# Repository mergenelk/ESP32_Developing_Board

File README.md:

# ESP32_Developing_Board
This project is unlicensed because it is very old.

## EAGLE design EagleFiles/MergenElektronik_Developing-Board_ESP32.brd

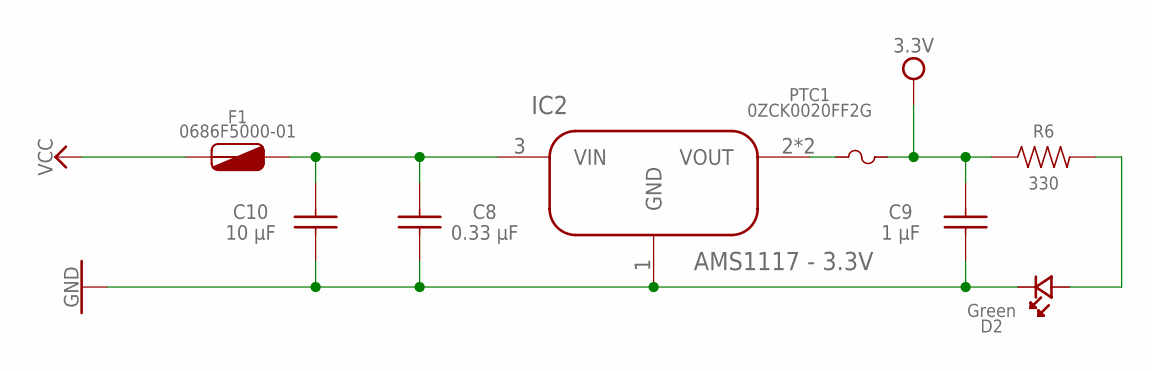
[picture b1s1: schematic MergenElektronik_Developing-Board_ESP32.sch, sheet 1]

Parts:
C8: 0.33 µF; 0603
C9: 1 µF; 0603
C10: 10 µF; 0603
D2: Green; 0603_GREEN
F1: 0686F5000-01; 0603
IC2: AMS1117 - 3.3V; SOT-223
PTC1: 0ZCK0020FF2G; 0805
R6: 330; 0603

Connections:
3V3: C9.1, PTC1.2, R6.1; also elsewhere on the board
GND: C8.2, C9.2, C10.2, D2.2 (KATOT), IC2.1 (GND); also elsewhere on the board
unnamed: D2.1 (ANOT), R6.2
unnamed: C8.1, C10.1, F1.2, IC2.3 (VIN)
unnamed: IC2.2 (VOUT), IC2.4 (VOUT), PTC1.1
VCC: F1.1; also elsewhere on the board

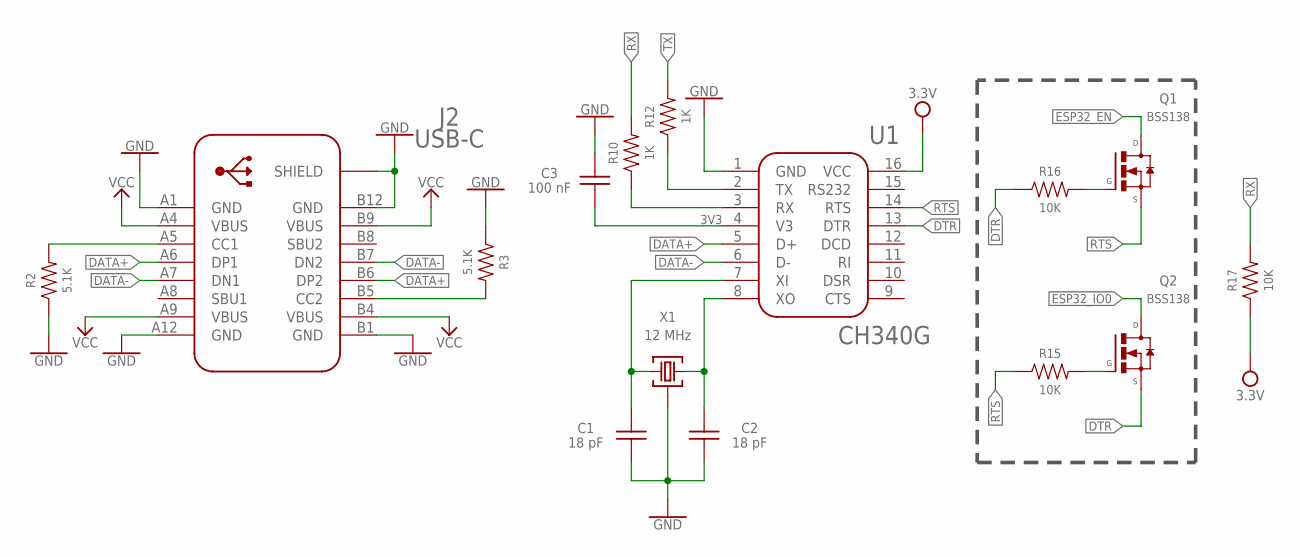
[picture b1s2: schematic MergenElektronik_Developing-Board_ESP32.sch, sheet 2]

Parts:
C1, C2: 18 pF; 0603
C3: 100 nF; 0603
J2: USB-C; USB4105
Q1, Q2: BSS138; SOT-23
R2, R3: 5.1K; 0603
R10, R12: 1K; 0603
R15, R16, R17: 10K; 0603
U1: CH340G; SOIC-16
X1: 12 MHz; 4-SMD

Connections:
3V3: C3.2, R17.1, U1.4 (V3), U1.16 (VCC); also elsewhere on the board
DATA+: J2.A6 (DP1), J2.B6 (DP2), U1.5 (D+)
DATA-: J2.A7 (DN1), J2.B7 (DN2), U1.6 (D-)
DTR: Q2.2 (S), R16.1, U1.13 (DTR)
ESP32_EN: Q1.3 (D); also elsewhere on the board
ESP32_IO0: Q2.3 (D); also elsewhere on the board
GND: C1.2, C2.2, C3.1, J2.A1 (GND), J2.A12 (GND), J2.B1 (GND), J2.B12 (GND), J2.SH1 (SHIELD), J2.SH2 (SHIELD), J2.SH3 (SHIELD), J2.SH4 (SHIELD), R2.1, R3.1, U1.1 (GND), X1.GND@1, X1.GND@2; also elsewhere on the board
unnamed: J2.A5 (CC1), R2.2
unnamed: J2.B5 (CC2), R3.2
unnamed: C1.1, U1.7 (XI), X1.3
unnamed: C2.1, U1.8 (XO), X1.1
unnamed: Q2.1 (G), R15.2
unnamed: R10.1, U1.3 (RX)
unnamed: R12.1, U1.2 (TX)
unnamed: Q1.1 (G), R16.2
RTS: Q1.2 (S), R15.1, U1.14 (RTS)
RX: R10.2, R17.2; also elsewhere on the board
TX: R12.2; also elsewhere on the board
VCC: J2.A4 (VBUS), J2.A9 (VBUS), J2.B4 (VBUS), J2.B9 (VBUS); also elsewhere on the board

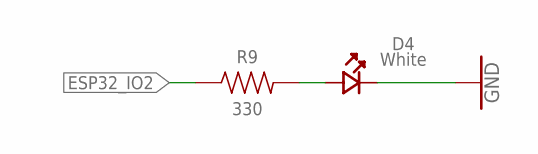
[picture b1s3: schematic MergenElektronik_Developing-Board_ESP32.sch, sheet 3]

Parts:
D4: White; 0603_WHİTE
R9: 330; 0603

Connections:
ESP32_IO2: R9.1; also elsewhere on the board
GND: D4.2 (KATOT); also elsewhere on the board
unnamed: D4.1 (ANOT), R9.2

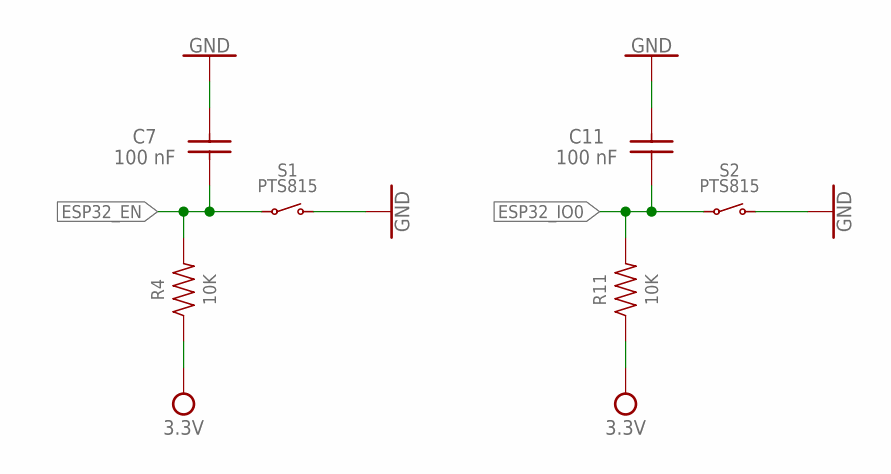
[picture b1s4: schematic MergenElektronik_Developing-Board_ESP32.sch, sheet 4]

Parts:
C7, C11: 100 nF; 0603
R4, R11: 10K; 0603
S1, S2: PTS815

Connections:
3V3: R4.1, R11.1; also elsewhere on the board
ESP32_EN: C7.2, R4.2, S1.1 (PASS1), S1.2 (PASS1); also elsewhere on the board
ESP32_IO0: C11.2, R11.2, S2.1 (PASS1), S2.2 (PASS1); also elsewhere on the board
GND: C7.1, C11.1, S1.3 (PASS2), S1.4 (PASS2), S2.3 (PASS2), S2.4 (PASS2); also elsewhere on the board

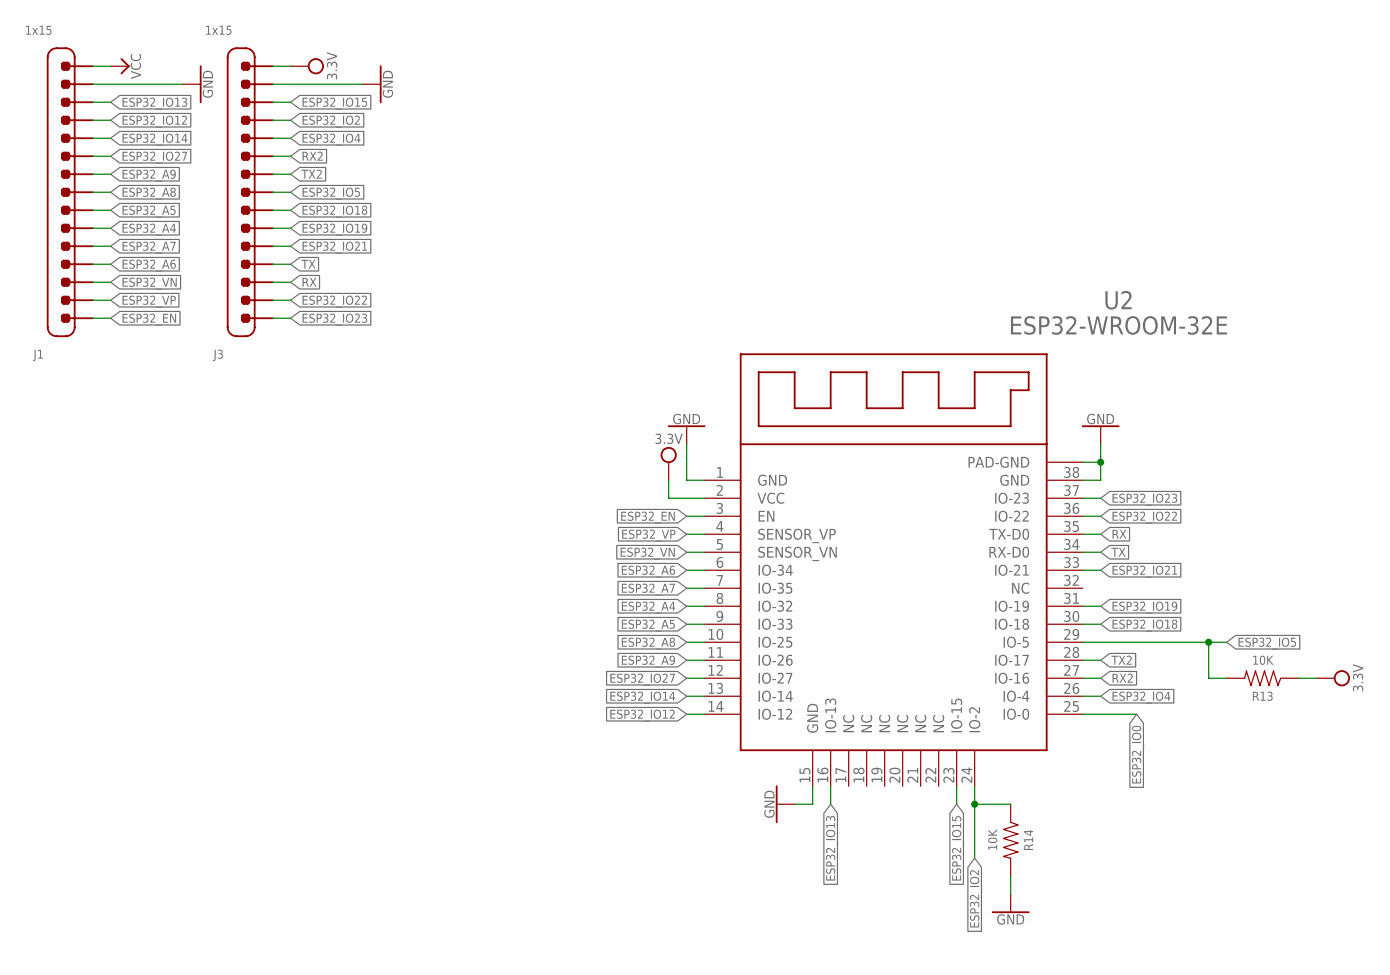
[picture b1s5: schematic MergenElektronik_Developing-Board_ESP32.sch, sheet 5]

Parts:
J1, J3: 1x15; HEADER_1X15
R13, R14: 10K; 0603
U2: ESP32-WROOM-32E; 38-SMD_MODULE

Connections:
3V3: J3.1, R13.1, U2.2 (VCC); also elsewhere on the board
ESP32_A4: J1.10, U2.8 (IO-32)
ESP32_A5: J1.9, U2.9 (IO-33)
ESP32_A6: J1.12, U2.6 (IO-34)
ESP32_A7: J1.11, U2.7 (IO-35)
ESP32_A8: J1.8, U2.10 (IO-25)
ESP32_A9: J1.7, U2.11 (IO-26)
ESP32_EN: J1.15, U2.3 (EN); also elsewhere on the board
ESP32_IO0: U2.25 (IO-0); also elsewhere on the board
ESP32_IO2: J3.4, R14.1, U2.24 (IO-2); also elsewhere on the board
ESP32_IO4: J3.5, U2.26 (IO-4)
ESP32_IO5: J3.8, R13.2, U2.29 (IO-5)
ESP32_IO12: J1.4, U2.14 (IO-12)
ESP32_IO13: J1.3, U2.16 (IO-13)
ESP32_IO14: J1.5, U2.13 (IO-14)
ESP32_IO15: J3.3, U2.23 (IO-15)
ESP32_IO18: J3.9, U2.30 (IO-18)
ESP32_IO19: J3.10, U2.31 (IO-19)
ESP32_IO21: J3.11, U2.33 (IO-21)
ESP32_IO22: J3.14, U2.36 (IO-22)
ESP32_IO23: J3.15, U2.37 (IO-23)
ESP32_IO27: J1.6, U2.12 (IO-27)
ESP32_VN: J1.13, U2.5 (SENSOR_VN)
ESP32_VP: J1.14, U2.4 (SENSOR_VP)
GND: J1.2, J3.2, R14.2, U2.1 (GND), U2.15 (GND), U2.38 (GND), U2.48 (PAD-GND), U2.P$1 (PAD-GND); also elsewhere on the board
RX: J3.13, U2.35 (TX-D0); also elsewhere on the board
RX2: J3.6, U2.27 (IO-16)
TX: J3.12, U2.34 (RX-D0); also elsewhere on the board
TX2: J3.7, U2.28 (IO-17)
VCC: J1.1; also elsewhere on the board

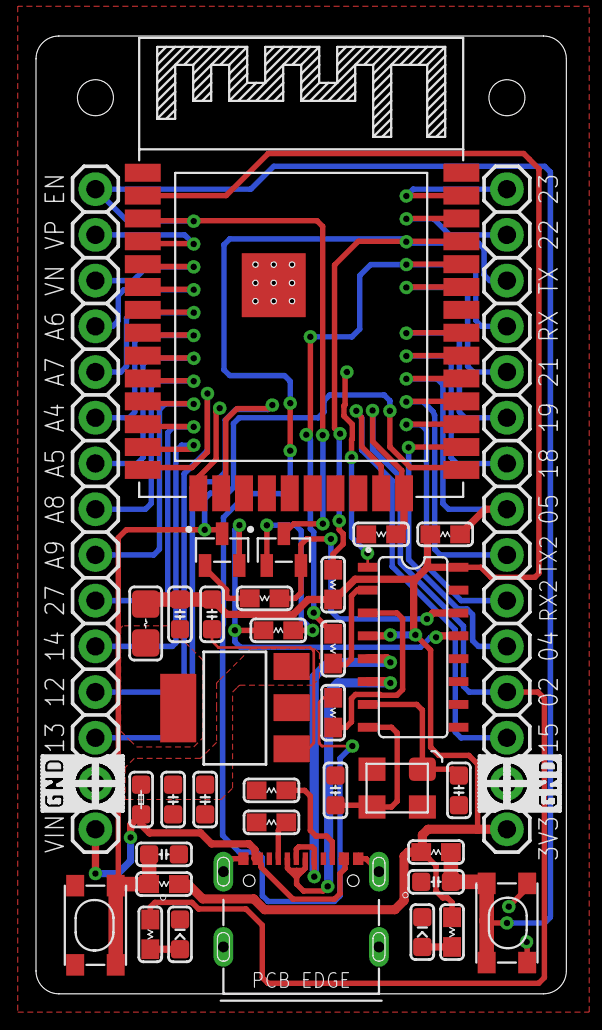
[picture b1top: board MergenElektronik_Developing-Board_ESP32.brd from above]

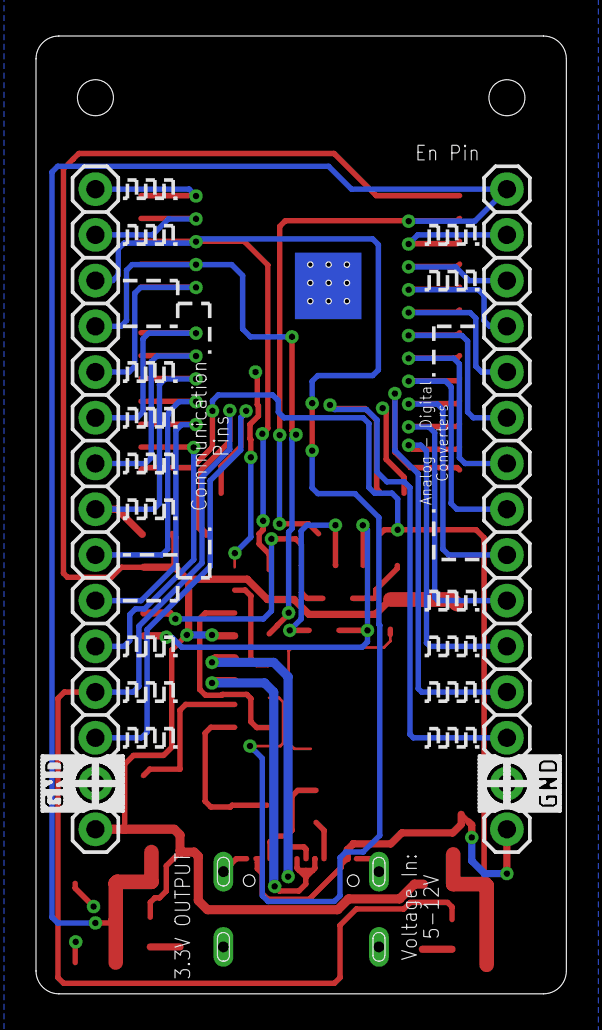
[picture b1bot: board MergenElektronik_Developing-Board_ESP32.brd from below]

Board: 2 copper layers, 29.5 x 53.2 mm, 36 parts (2 on the bottom side), 46 nets.

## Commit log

2025-02-17 17/02/2025
